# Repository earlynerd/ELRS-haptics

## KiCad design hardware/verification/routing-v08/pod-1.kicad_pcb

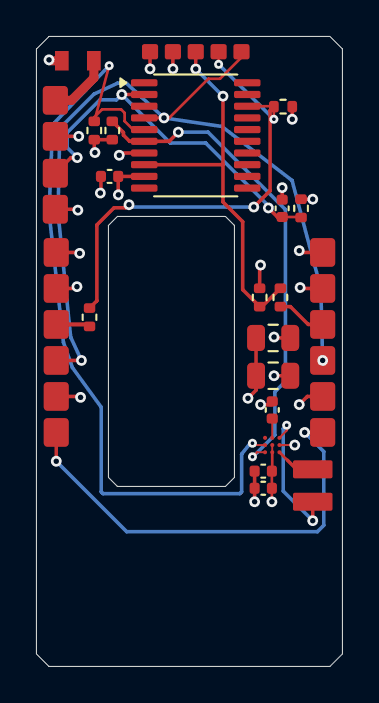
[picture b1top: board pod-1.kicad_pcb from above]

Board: 4 copper layers, 17.0 x 35.0 mm, 23 parts (0 on the bottom side), 16 nets.

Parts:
C8, C9, C110: 100n; C_0402_1005Metric
C10: 1u; C_0402_1005Metric
C111: 10u; C_0805_2012Metric
C112: 10n; C_0402_1005Metric
C113: 22u 10V X5R; C_0805_2012Metric
F101: 250mA FAST; Fuse_Littelfuse_467_0603
J104: CHAIN IN; WirePads_6_P2mm
J105: CHAIN OUT; WirePads_6_P2mm
J106: ICE / INITIAL FLASH; WirePads_5_P1.27mm
J107: NTC (optional); WirePads_2_P2mm
J201: PROTECTED CELL 90mAh; WirePads_2_P2mm
M2: VLV041235L; Vybronics_VLV041235L_FPC_Contact_Draft
R10, R11: 4.7k; R_0402_1005Metric
R110: 0; R_0402_1005Metric
R111: 33; R_0402_1005Metric
R112, R113: 100k; R_0402_1005Metric
R115: 10k 1%; R_0402_1005Metric
U4: DRV2625; DRV2625_YFF_9_0.4mm
U19: M2003FC1AE; TSSOP-20_4.4x6.5mm_P0.65mm

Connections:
/Eight ring pods/Pod 1 / U19/CELL_POS: F101.1, J201.1
/Eight ring pods/Pod 1 / U19/CELL_TEMP: C112.1, J107.1, R115.2, U19.2
/Eight ring pods/Pod 1 / U19/DRV_REG: C9.1, U4.A2
/Eight ring pods/Pod 1 / U19/LOCAL_SCL: R11.2, U4.C1, U19.6
/Eight ring pods/Pod 1 / U19/LOCAL_SDA: R10.2, U4.B1, U19.5
/Eight ring pods/Pod 1 / U19/LRA_N: M2.2, U4.C3
/Eight ring pods/Pod 1 / U19/LRA_P: M2.1, U4.A3
/Eight ring pods/Pod 1 / U19/UART_RX_LOCAL: J106.4, R110.2, R112.2, U19.18
/Eight ring pods/Pod 1 / U19/UART_TX_LOCAL: J106.3, R111.1, R113.2, U19.8
GND: C8.2, C9.2, C10.2, C110.2, C111.2, C112.2, C113.2, J104.2, J105.2, J106.2, J107.2, J201.2, U4.B3, U19.7
POD_3V3: C8.1, C10.1, C110.1, C111.1, C113.1, J104.1, J105.1, J106.1, R10.1, R11.1, R112.1, R113.1, R115.1, U4.B2, U4.C2, U19.9
RING_D1: J104.3, R110.1
RING_D2: J105.3, R111.2
RING_RETURN: J104.6, J105.6
RING_nRESET: J104.4, J105.4, J106.5, U19.4
VBAT: F101.2, J104.5, J105.5
